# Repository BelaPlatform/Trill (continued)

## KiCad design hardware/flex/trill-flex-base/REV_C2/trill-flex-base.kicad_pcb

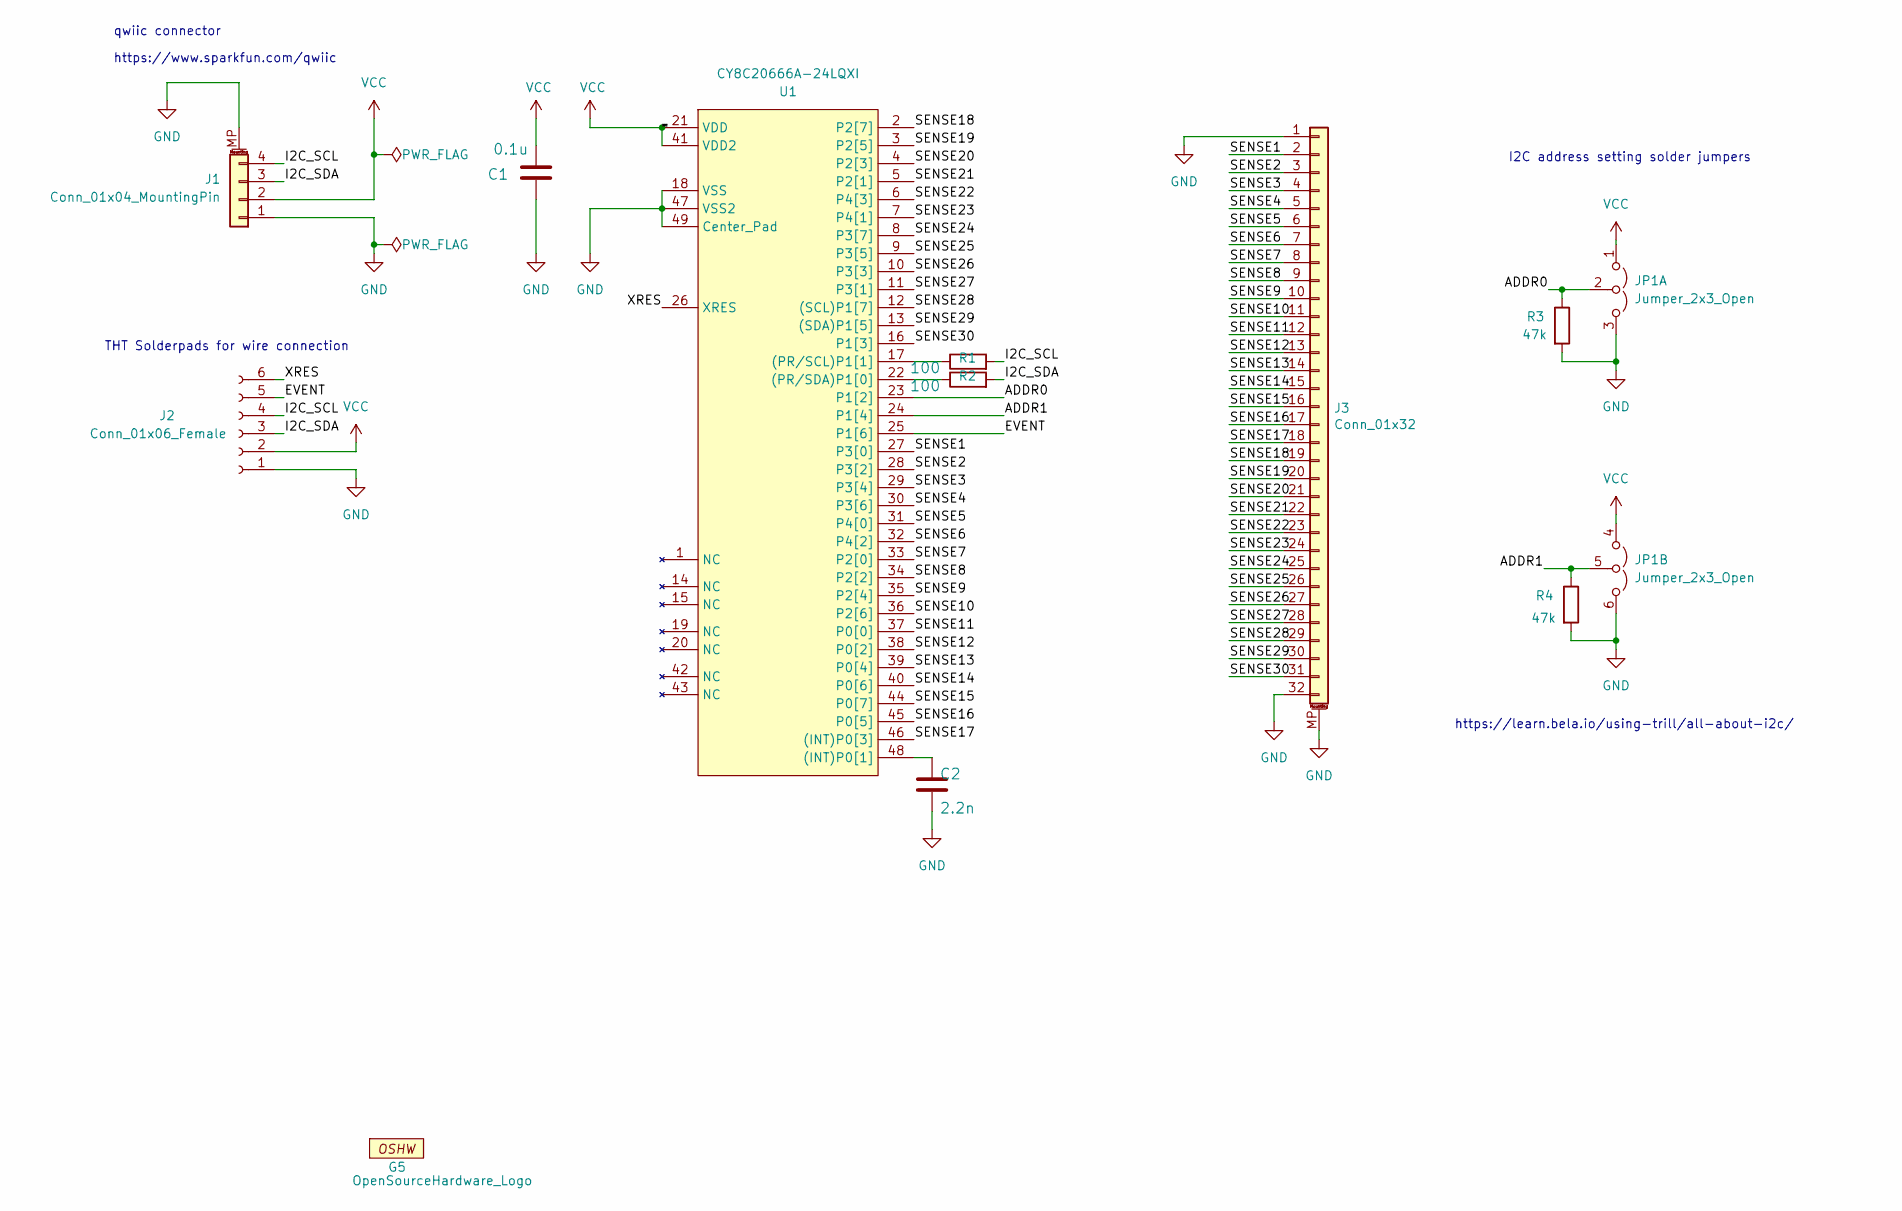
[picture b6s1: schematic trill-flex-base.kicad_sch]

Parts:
C1: 0.1u; C_0402_1005Metric
C2: 2.2n; C_0402_1005Metric
G5: OpenSourceHardware_Logo
J1: Conn_01x04_MountingPin; qwiic_horizontal_SMD
J2: Conn_01x06_Female; I2C+EVT_RST_Wire_connector_THT
J3: Conn_01x32; Hirose_FH12-32S-0.5SH_1x32-1MP_P0.50mm_Horizontal
JP1: Jumper_2x3_Open; SolderJumper-2x3_P1.3mm_Open_Pad1.0x1.5mm
R1, R2: 100; R_0402_1005Metric
R3, R4: 47k; R_0402_1005Metric
U1: CY8C20666A-24LQXI; QFN-48-1EP_6x6mm_P0.4mm_EP4.6x4.6mm

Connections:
/ADDR0: JP1.2 (C), R3.1, U1.23 (P1[2])
/ADDR1: JP1.5 (A), R4.1, U1.24 (P1[4])
/EVENT: J2.5, U1.25 (P1[6])
/I2C_SCL: J1.4, J2.4, R1.2
/I2C_SDA: J1.3, J2.3, R2.2
/SENSE1: J3.2, U1.27 (P3[0])
/SENSE2: J3.3, U1.28 (P3[2])
/SENSE3: J3.4, U1.29 (P3[4])
/SENSE4: J3.5, U1.30 (P3[6])
/SENSE5: J3.6, U1.31 (P4[0])
/SENSE6: J3.7, U1.32 (P4[2])
/SENSE7: J3.8, U1.33 (P2[0])
/SENSE8: J3.9, U1.34 (P2[2])
/SENSE9: J3.10, U1.35 (P2[4])
/SENSE10: J3.11, U1.36 (P2[6])
/SENSE11: J3.12, U1.37 (P0[0])
/SENSE12: J3.13, U1.38 (P0[2])
/SENSE13: J3.14, U1.39 (P0[4])
/SENSE14: J3.15, U1.40 (P0[6])
/SENSE15: J3.16, U1.44 (P0[7])
/SENSE16: J3.17, U1.45 (P0[5])
/SENSE17: J3.18, U1.46 ((INT)P0[3])
/SENSE18: J3.19, U1.2 (P2[7])
/SENSE19: J3.20, U1.3 (P2[5])
/SENSE20: J3.21, U1.4 (P2[3])
/SENSE21: J3.22, U1.5 (P2[1])
/SENSE22: J3.23, U1.6 (P4[3])
/SENSE23: J3.24, U1.7 (P4[1])
/SENSE24: J3.25, U1.8 (P3[7])
/SENSE25: J3.26, U1.9 (P3[5])
/SENSE26: J3.27, U1.10 (P3[3])
/SENSE27: J3.28, U1.11 (P3[1])
/SENSE28: J3.29, U1.12 ((SCL)P1[7])
/SENSE29: J3.30, U1.13 ((SDA)P1[5])
/SENSE30: J3.31, U1.16 (P1[3])
/XRES: J2.6, U1.26 (XRES)
GND: C1.1, C2.2, J1.1, J1.MP (MountPin), J2.1, J3.1, J3.32, J3.MP (MountPin), JP1.3 (B), JP1.6 (B), R3.2, R4.2, U1.18 (VSS), U1.47 (VSS2), U1.49 (Center_Pad)
unnamed: C2.1, U1.48 ((INT)P0[1])
unnamed: R1.1, U1.17 ((PR/SCL)P1[1])
unnamed: R2.1, U1.22 ((PR/SDA)P1[0])
VCC: C1.2, J1.2, J2.2, JP1.1 (A), JP1.4 (A), U1.21 (VDD), U1.41 (VDD2)

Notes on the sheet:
https://learn.bela.io/using-trill/all-about-i2c/
qwiic connector
I2C address setting solder jumpers
https://www.sparkfun.com/qwiic
THT Solderpads for wire connection

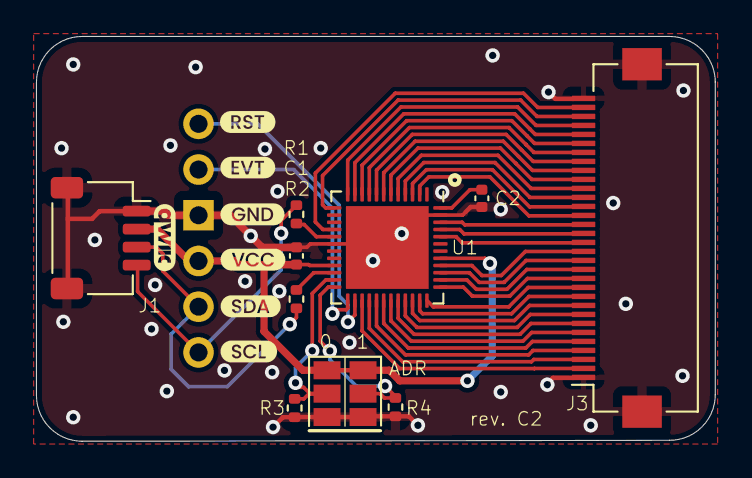
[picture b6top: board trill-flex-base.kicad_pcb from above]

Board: 2 copper layers, 37.7 x 22.5 mm, 12 parts (1 on the bottom side), 41 nets.

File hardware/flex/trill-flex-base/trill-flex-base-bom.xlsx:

Name | Quantity | Value | Package | Description | Mouser # | Digi-Key # | Datasheet / Notes
C1 | 1 | 0.1uF | "0603" | Capacitor ceramic 0402; standard bypass cap 5V+
C2 | 1 | 2.2nF | "0603" | Capacitor ceramic 0402; 5% | 81-GRM36X222J50
IC1 | 1 | CY8C20636A-24LTXI | 48-QFN, 7x7mm | IC Cypress SoC | 727-CY8C20636A24LTXI
J1 | 1 | Grove connector, vertical SMT | SMD | 4-pin 2mm vertical Grove connector (Seeed)
R1-R2 | 2 | 100 ohm | "0603" | Resistor 0603 (standard part)
R3-R4 | 2 | 47k ohm | "0603" | Resistor 0603 (standard part)
Total | 8

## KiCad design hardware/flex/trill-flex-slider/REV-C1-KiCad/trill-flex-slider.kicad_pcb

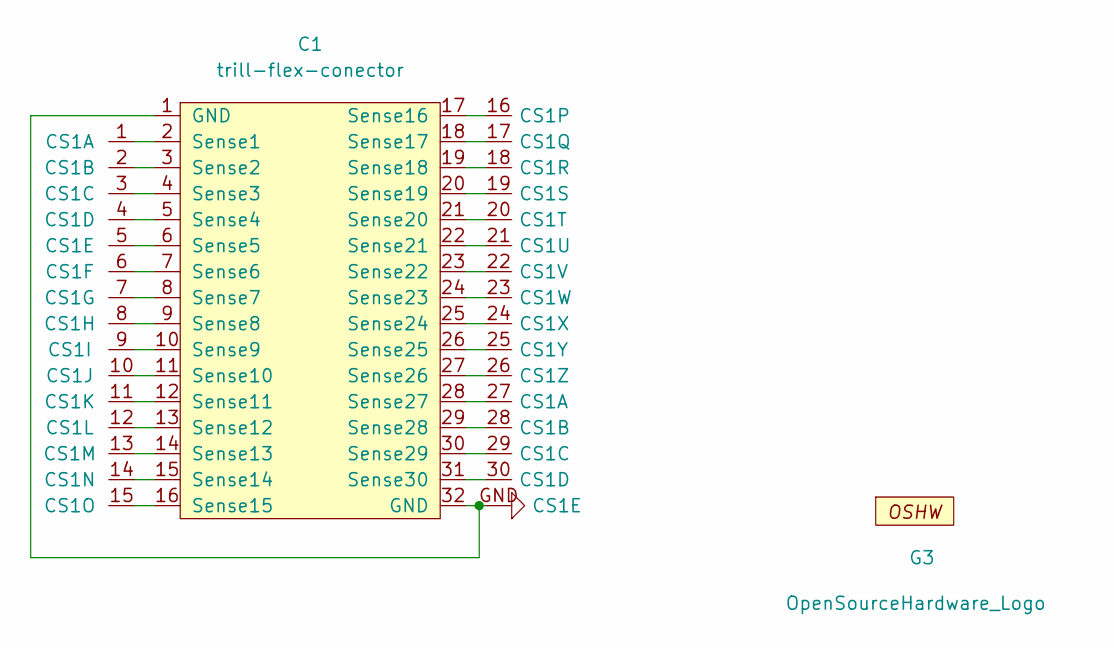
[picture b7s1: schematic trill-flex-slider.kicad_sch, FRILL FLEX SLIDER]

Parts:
C1: trill-flex-conector; trill_flex_connector_long
CS1: TRILL_FLEX-30_CapSense; TRILL_FLEX_CapSense
G3: OpenSourceHardware_Logo

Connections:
unnamed: C1.1 (GND), C1.32 (GND), CS1.GND
unnamed: C1.2 (Sense1), CS1.1
unnamed: C1.3 (Sense2), CS1.2
unnamed: C1.4 (Sense3), CS1.3
unnamed: C1.5 (Sense4), CS1.4
unnamed: C1.6 (Sense5), CS1.5
unnamed: C1.7 (Sense6), CS1.6
unnamed: C1.8 (Sense7), CS1.7
unnamed: C1.9 (Sense8), CS1.8
unnamed: C1.10 (Sense9), CS1.9
unnamed: C1.11 (Sense10), CS1.10
unnamed: C1.12 (Sense11), CS1.11
unnamed: C1.13 (Sense12), CS1.12
unnamed: C1.14 (Sense13), CS1.13
unnamed: C1.15 (Sense14), CS1.14
unnamed: C1.16 (Sense15), CS1.15
unnamed: C1.17 (Sense16), CS1.16
unnamed: C1.18 (Sense17), CS1.17
unnamed: C1.19 (Sense18), CS1.18
unnamed: C1.20 (Sense19), CS1.19
unnamed: C1.21 (Sense20), CS1.20
unnamed: C1.22 (Sense21), CS1.21
unnamed: C1.23 (Sense22), CS1.22
unnamed: C1.24 (Sense23), CS1.23
unnamed: C1.25 (Sense24), CS1.24
unnamed: C1.26 (Sense25), CS1.25
unnamed: C1.27 (Sense26), CS1.26
unnamed: C1.28 (Sense27), CS1.27
unnamed: C1.29 (Sense28), CS1.28
unnamed: C1.30 (Sense29), CS1.29
unnamed: C1.31 (Sense30), CS1.30

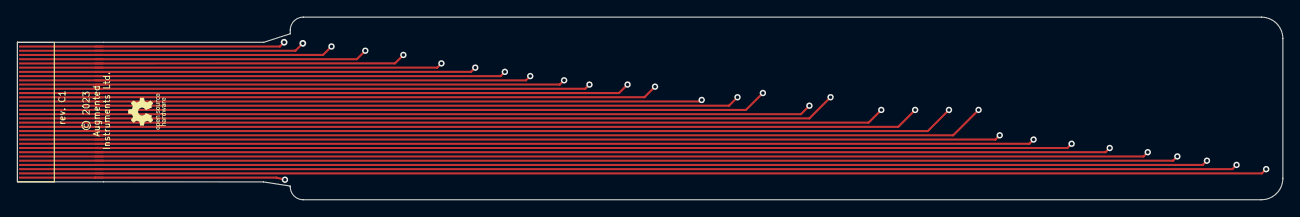
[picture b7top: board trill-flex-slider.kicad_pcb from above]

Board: 2 copper layers, 149.6 x 21.5 mm, 3 parts (0 on the bottom side), 31 nets.

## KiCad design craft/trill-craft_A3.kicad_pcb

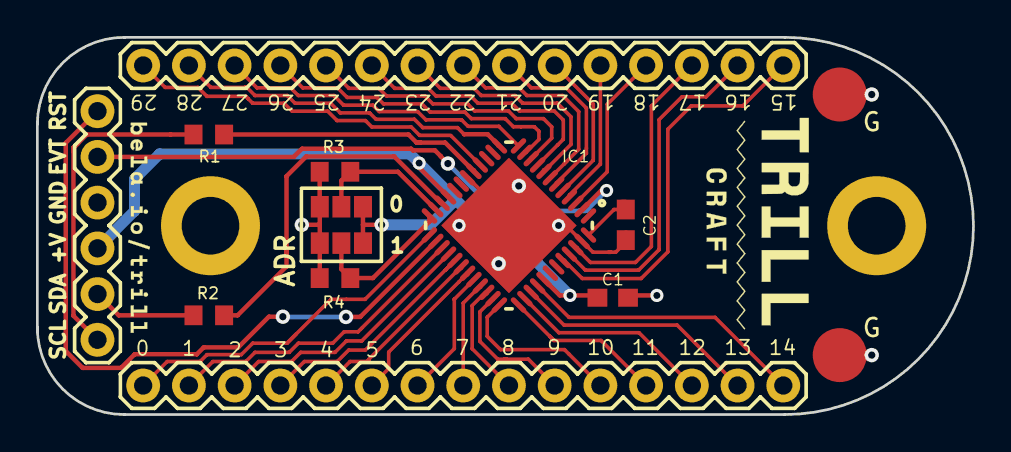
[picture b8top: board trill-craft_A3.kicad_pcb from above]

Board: 2 copper layers, 52.0 x 21.0 mm, 14 parts (0 on the bottom side), 41 nets.

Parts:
C1, C2: C-USC0603; C0603
G: Conn_01x01_Female; Circular_pad_smd
G#2: Conn_01x01_Female; Circular_pad_smd
IC1: CY8C206X6A; QFN48-LEADS
JP1: M06SILK_FEMALE_PTH; 1X06
JP3, JP4: Conn_01x15_Female; 1X15
Jumper0, Jumper1: Conn_01x03_Female; DOUBLE_SOLDER_JUMPER
R1, R2, R3, R4: R-EU_R0603; R0603

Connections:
/EVENT: IC1.2, JP1.2
/I2C_SCL: JP1.6, R1.2
/I2C_SDA: JP1.5, R2.2
/XRES: IC1.26, JP1.1
GND: C1.1, C2.2, G.1, G#2.1, IC1.18, IC1.47, IC1.EXP, JP1.3, Jumper0.3, Jumper1.3, R3.2, R4.2
unnamed: C2.1, IC1.48
unnamed: IC1.3, JP3.4
unnamed: IC1.4, JP3.5
unnamed: IC1.5, JP3.6
unnamed: IC1.6, JP3.7
unnamed: IC1.7, JP3.8
unnamed: IC1.8, JP3.9
unnamed: IC1.9, JP3.10
unnamed: IC1.10, JP3.11
unnamed: IC1.11, JP3.12
unnamed: IC1.12, JP3.13
unnamed: IC1.13, JP3.14
unnamed: IC1.16, JP3.15
unnamed: IC1.17, R1.1
unnamed: IC1.22, R2.1
unnamed: IC1.23, Jumper0.2, R3.1
unnamed: IC1.24, Jumper1.2, R4.1
unnamed: IC1.25, JP4.1
unnamed: IC1.27, JP4.2
unnamed: IC1.28, JP4.3
unnamed: IC1.29, JP4.4
unnamed: IC1.30, JP4.5
unnamed: IC1.31, JP4.6
unnamed: IC1.32, JP4.7
unnamed: IC1.33, JP4.8
unnamed: IC1.34, JP4.9
unnamed: IC1.35, JP4.10
unnamed: IC1.36, JP4.11
unnamed: IC1.37, JP4.12
unnamed: IC1.38, JP4.13
unnamed: IC1.39, JP4.14
unnamed: IC1.40, JP4.15
unnamed: IC1.44, JP3.1
unnamed: IC1.45, JP3.2
unnamed: IC1.46, JP3.3
VCC: C1.2, IC1.21, IC1.41, JP1.4, Jumper0.1, Jumper1.1

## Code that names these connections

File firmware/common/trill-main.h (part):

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#define I2C_ADDR_PIN0			(1 << 2)
#define I2C_ADDR_PIN1			(1 << 4)

// Pin for output EVENT signal
#if (ID_DEVICE_TYPE == ID_DEVICE_CRAFT)
#define EVENT_PORT_DATA			PRT2DR
#define EVENT_PORT_DIR0			PRT2DM0
#define EVENT_PORT_DIR1			PRT2DM1
#define EVENT_PIN			(1 << 7)
#else
#define EVENT_PORT_DATA			PRT1DR
#define EVENT_PORT_DIR0			PRT1DM0
#define EVENT_PORT_DIR1			PRT1DM1
#define EVENT_PIN			(1 << 6)
#endif

// Max number of touches to support
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	BYTE address = BASELINE_I2C_ADDRESS;
	BYTE counter;

	// I2C address is determined based on status of ADDR0 and ADDR1 pins
	// which could be in three states: open, tied high, tied low. We first
	// read with a pullup resistor to distinguish between open and tied low;
	// then we read with high-Z to distinguish between open and tied high.
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}

void setEventPin(void) {
	EVENT_PORT_DATA |= EVENT_PIN;
}
void clearEventPin(void) {
	EVENT_PORT_DATA &= ~EVENT_PIN;
}
// for debugging purposes, make it easy to use the address pins as additional
// outputs
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#endif // ID_DEVICE_RING
	WORD posEndOfLoop = (LAST_SENSOR_V - FIRST_SENSOR_V) << SLIDER_BITS;

	// Detect the I2C address from the ADDR0 and ADDR1 pins
	address = detectI2cAddress();

	// Set event pin to strong output (low): DIR1:0 = 01
	EVENT_PORT_DIR1 &= ~EVENT_PIN;
	EVENT_PORT_DIR0 |= EVENT_PIN;
	clearEventPin();

#ifdef ADDRESS_PINS_DEBUG
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				// Copy the two button readings to the end
				wCommBufferInactive[COMM_DATA_OFFSET_WORDS + 2*MAX_NUM_CENTROIDS] = CSD_waSnsDiff[28];
				wCommBufferInactive[COMM_DATA_OFFSET_WORDS + 2*MAX_NUM_CENTROIDS + 1] = CSD_waSnsDiff[29];
				// also set the event pin if any of the "button" pins is active
				bActivityDetected = bActivityDetected || CSD_waSnsDiff[28] || CSD_waSnsDiff[29];
#endif // RING
				break;
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		wCommBufferInactive = wCommBuffers[!bCurrentCommBuffer];
#endif // BUFFER_SWAP

		// If any activity was detected, turn on the event pin, which will
		// be unconditionally cleared elsewhere.
		// An external device monitoring this pin should be looking for a
		// rising edge denoting new data available.
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
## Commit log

2020-06-23 Hardware and datasheet
2020-07-02 Moved hw to subfolder
2020-07-02 Added firmware
2020-11-19 Added BOMs
    Closes https://github.com/BelaPlatform/Trill/issues/2
2021-03-02 Updated datasheet with Trill Flex
2021-03-03 Added Trill Flex files
2021-03-09 fix outline in Edge.cuts layer to be continuous
2022-10-21 KiCad Eagle import or Trill square, gitignore
2023-02-09 Added FLEX to common headers
2023-02-09 Added flex.
    Now on par with Trill_firmware@3d9a512dbde8e439073c2b0662544f1300c713dc
2023-08-03 move datasheet in subfolder
2023-08-03 add REV C datasheet
2023-08-03 renamed REV C datasheet
2023-08-03 update datasheet
2023-08-03 datasheet from 45443b05c4b4d137e50fff726424ba4e64555c03
2023-08-24 Placed REV_C datasheet in place of the old link which is all over the internet
2023-10-19 added current source files for rev C series
2023-10-24 Update README.md
    updated license from CC-BY-SA 3 to 4
2023-10-24 Update README.md
    updated readme to contain same wording and info as the datasheet.
2023-10-24 Update README.md
    removed latex escape character in url
2023-10-24 Update README.md
    let's use mouser.com instead of mouser.it
2023-10-26 added added trill craft as a symbol, footprint and 3dmodel. fixes #5
2023-10-26 relative path to 3dmodel
2023-11-01 updated datasheet to V.1.1
2024-11-08 Datasheet version 1.3
2024-11-08 Updating final v1.3 datasheet
2025-01-31 adding all trill craft footprints
2025-01-31 adding REV3 of Craft design
2025-01-31 Added github action to keep legacy master branch up to date with latest main
2025-02-03 moving remaining craft footprint from general footprint library
2025-02-03 pushing datasheet rev 1.3
2025-02-03 datasheet rev 1.3 in subfolder too
